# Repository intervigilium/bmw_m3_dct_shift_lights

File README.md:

# BMW M3 DCT Cluster Shift Lights Retrofit

## BMW M3 DCT Cluster
The M3 DCT instrument cluster has a series of 8 shift lights above the
tachometer. These shift lights are normally not active, and do not appear to
be possible to activate without having the DCT itself. Fortunately, the
cluster's LEDs can be driven by attaching leads to the test points on the
ground side, as the LEDs are connected to an onboard 5V rail for power, and
a TI 6C596G4 8-bit shift register which acts as a current sink to ground.
Grounding each of these LED pairs will light up the corresponding pair.

## Retrofit circuit
Instead of attempting to drive the LEDs using the onboard TI 6C596 shift
register, we can just connect the LEDs to a shift register of our own and
connect that to an Arduino. The sketch here assumes that the shift register
is a TI 6C596 as well, and is configured using pins D3-D5, D18-D19. Engine
RPM for the BMW E9X series appears to be present on OBD2 port pin 9 as a 12V
square wave. This circuit utilizes the 12V RPM signal input circuit from
the Chippernut digital shift light project to read the signal, as well as
the 5V buck regulator input circuit to provide power.

## Cluster modifications
The M3 DCT cluster modifications necessary are detailed in the
`m3_dct_cluster_gnd_points.jpeg` file. Ignore the leads from the LEDs
themselves. The important points are circled in black, and correspond to the
ground points for the LED pairs. It is necessary to attach leads to these
ground points ONLY. You MUST attach leads to the test points AFTER the 127 Ohm
resistor (the highlighted points ONLY), not before. Failure to follow this
instruction will result in burning out the LEDs due to overcurrent.
You will also need to cut a small hole in the cluster enclosure to allow the LED
ground lines to connect to the Arduino.

## Schematic
The included `m3_dct_shift_lights.sch` file can be opened with any Eagle
schematic compatible program. The schematic only includes the circuit necessary
to read the RPM and control the LEDs. It does NOT include the necessary circuit
to independently power the Arduino from the car's +12V power sources. The
Chippernut development board
(<https://www.chippernut.com/store/p31/Chipperkit.html>) comes with a power
pack consisting of a 5V buck converter that can be used for this purpose.

## Components
The included `bom_m3_dct_shift_lights.csv` file contains the list of parts
necessary to build the circuit. The BOM list can easily purchased on Digikey.
It does not include the Arduino or a board to mount all the components. I
highly suggest using the above linked Chippernut development board pack, as it
comes with the 5V buck converter as well as a development board, Arduino nano,
and enclosure for installation.

## Installation
You will need to tap pin 9 of the OBD2 port for the tachometer signal. This
needs to be connected where the schematic says "To OBD2 Pin 9". You will also
need to provide power and ground, as well as connecting the 8 LED ground lines
from the M3 DCT cluster to the shift register (Refer to schematic where it
details the LED pairs with the notes that these are on board). I suggest
tapping +12V power and ground from the cluster connector pins 9 (+12V) and
18 (ground). I suspect the circuit must be connected to the cluster's ground
in order for the LEDs to function. The Arduino and wires can be tucked into
the driver's footwell under the panel. I chose to zip tie it near the firewall.

## Software Notes
The Arduino sketch has a few constants that can be customized to suit your
needs. The activation RPM and the maximum RPM values can be found at the top
of the file with the names `kActivationRpm` and `kMaxRpm`, respectively. The
`kActivationRpm` variable sets the RPM value at which the first LED will light.
The `kMaxRpm` variable sets the RPM value at which the all the LEDs will start
to flash. Any RPM value above the `kMaxRpm` value will mean the LEDs continue
to flash until the RPM drops below the threshold.

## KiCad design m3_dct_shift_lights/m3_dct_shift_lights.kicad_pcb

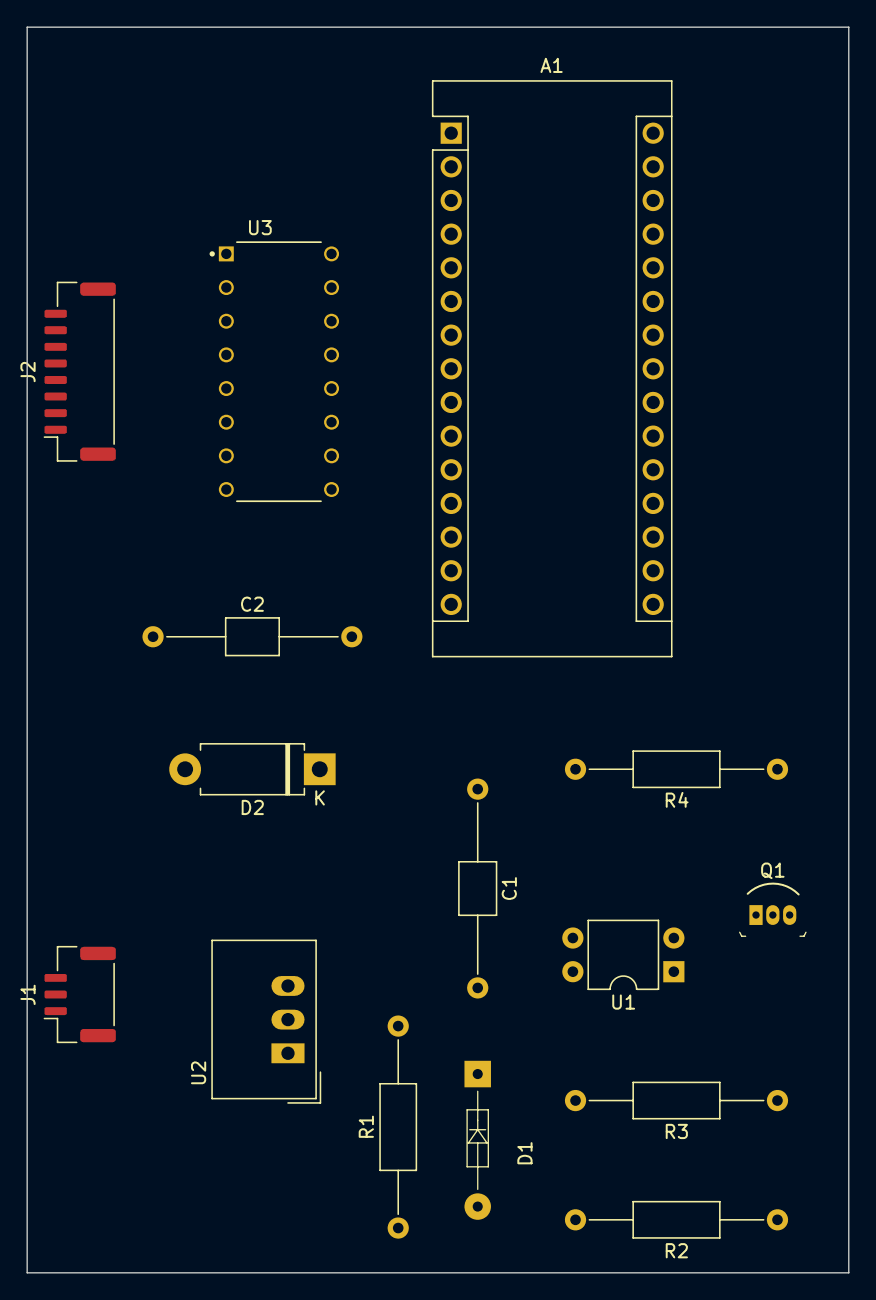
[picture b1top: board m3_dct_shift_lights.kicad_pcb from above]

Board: 2 copper layers, 62.0 x 94.0 mm, 15 parts (0 on the bottom side), 22 nets, no tracks yet.

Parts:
A1: Arduino_Nano_v3.x; Arduino_Nano
C1: 100uF; C_Axial_L3.8mm_D2.6mm_P15.00mm_Horizontal
C2: 1000uF; C_Axial_L3.8mm_D2.6mm_P15.00mm_Horizontal
D1: 1N4148; Diode_DO-35_P10mm
D2: D_Schottky; D_DO-15_P10.16mm_Horizontal
J1: Conn_01x03; JST_GH_SM03B-GHS-TB_1x03-1MP_P1.25mm_Horizontal
J2: Conn_01x08; JST_GH_SM08B-GHS-TB_1x08-1MP_P1.25mm_Horizontal
Q1: 2N3906; TO-92-3
R1: 7.5k; R_Axial_DIN0207_L6.3mm_D2.5mm_P15.24mm_Horizontal
R2, R4: 10k; R_Axial_DIN0207_L6.3mm_D2.5mm_P15.24mm_Horizontal
R3: 47k; R_Axial_DIN0207_L6.3mm_D2.5mm_P15.24mm_Horizontal
U1: SFH617A-2; DIP-4_W7.62mm
U2: TSR_1-2450; Converter_DCDC_TRACO_TSR-1_THT
U3: TPIC6C596N; DIP794W45P254L1969H508Q16

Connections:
+12V: D2.2 (A), J1.3
GND: A1.4 (GND), C1.2, C2.2, D1.2, J1.2, R4.2, U1.2, U1.3, U2.2 (GND), U3.16 (GND)
unnamed: A1.5 (D2), Q1.3 (C), R4.1
unnamed: A1.6 (D3), U3.15 (SRCK)
unnamed: A1.8 (D5), U3.2 (SERIN)
unnamed: A1.9 (D6), U3.10 (RCK)
unnamed: A1.21 (A2), U3.8 (G)
unnamed: A1.22 (A3), U3.7 (CLR)
unnamed: C1.1, D2.1 (K), U2.1 (Vin)
unnamed: D1.1, R1.2, U1.1
unnamed: J1.1, R1.1
unnamed: J2.1, U3.3 (DRAIN0)
unnamed: J2.2, U3.4 (DRAIN1)
unnamed: J2.3, U3.5 (DRAIN2)
unnamed: J2.4, U3.6 (DRAIN3)
unnamed: J2.5, U3.11 (DRAIN4)
unnamed: J2.6, U3.12 (DRAIN5)
unnamed: J2.7, U3.13 (DRAIN6)
unnamed: J2.8, U3.14 (DRAIN7)
unnamed: Q1.2 (B), R3.1
unnamed: R2.2, R3.2, U1.4
VCC: A1.27 (+5V), C2.1, Q1.1 (E), R2.1, U2.3 (Vout), U3.1 (VCC)

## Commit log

2021-03-21 arduino: Add initial m3 cluster power tester
2021-04-04 power_tester: Light all LEDs up to index
2021-04-04 power_tester: Make pin constants constants
2021-04-04 power_tester: Only allow valid inputs to light function
2021-04-04 power_tester: Fix constant naming
2021-04-04 power_tester: Move serial input pin to 5
    * External interrupt must be on pin 2/3
2021-04-04 power_tester: Read RPM pin
2021-04-04 power_tester: Move shift register pin setup to function
2021-04-04 power_tester: Move RPM pin setup to function
2021-04-04 power_tester: Make RPM per pulse var const
2021-04-04 power_tester: Activate LEDs based on RPM
2021-04-04 power_tester: Remove unused variable
2021-04-04 power_tester: Add RPM scaling test mode
2021-04-04 power_tester: Reverse RPM tester direction
2021-04-04 power_tester: Disable lights if no lights need lighting
2021-04-04 power_tester: Illuminate debug RPM for 200ms
2021-04-04 power_tester: Make blink timing comment accurate
2021-04-04 power_tester: Fix last LED enable at max RPM
    * Account for the fact that we want the last LED segment to be on just
    before it reaches max RPM, as once max RPM is reached, the system will
    begin to blink all the LEDs.
2021-04-04 power_tester: Ensure all illumination paths cycle for 200ms
2021-04-04 power_tester: Cycle between activation and max RPM only when debugging
2021-04-04 power_tester: Use constant for illumination time
2021-04-04 power_tester: Move debug RPM generation to function
2021-04-04 power_tester: Add comment about interrupt pins
2021-04-04 power_tester: Reduce startup clear delay
2021-04-09 Rename project
2021-04-09 Add README
2021-04-09 Print RPM periodically
2021-04-10 Update pins for actual circuit board
2021-04-10 Reduce frequency of debug output
2021-04-11 Guard gNumCycles usage by serial check
2021-04-11 Fix debug RPM initial state
2021-04-11 Convert RPM debug code to struct
2021-04-11 Convert serial debug code to struct
2021-04-11 Convert RPM tachometer code to struct
2021-04-12 Allow Arduino to power down if no RPM signal present
2021-04-12 Move RPM pin into Tach struct as well
2021-04-12 Add circuit schematic
2021-04-12 Add parts BOM from Digikey
2021-04-12 Add cluster ground points
2021-04-12 Update README with more information
2021-04-12 Update schematic, move to center of sheet
2021-10-10 totem_lights: Add totem lights project
2021-10-10 neopixel: Import neopixel library
2021-10-10 totem_lights: fix file hierarchy
2021-10-10 totem_lights: neopixel sample code import
2021-10-11 totem_lights: Implement various lighting effects
2021-10-16 totem_lights: Switch mode using reset
2022-05-02 pack_lights: Import gemma m0 circuitpython code
2022-05-02 pack_lights: Use simple neopixel 12
2022-05-02 pack_lights: Replace with dynamic listening code
2022-05-06 pack_lights: Use full LED range
2022-05-06 pack_lights: lower brightness
2022-05-06 pack_lights: reformat with black
2022-05-08 import additional libraries
2022-05-08 pack_lights: Add basic FFT max value fill
2022-05-08 pack_lights: Disable status dotstar
2023-12-27 Add gitignore for kicad files
2023-12-27 Save initial kicad project
